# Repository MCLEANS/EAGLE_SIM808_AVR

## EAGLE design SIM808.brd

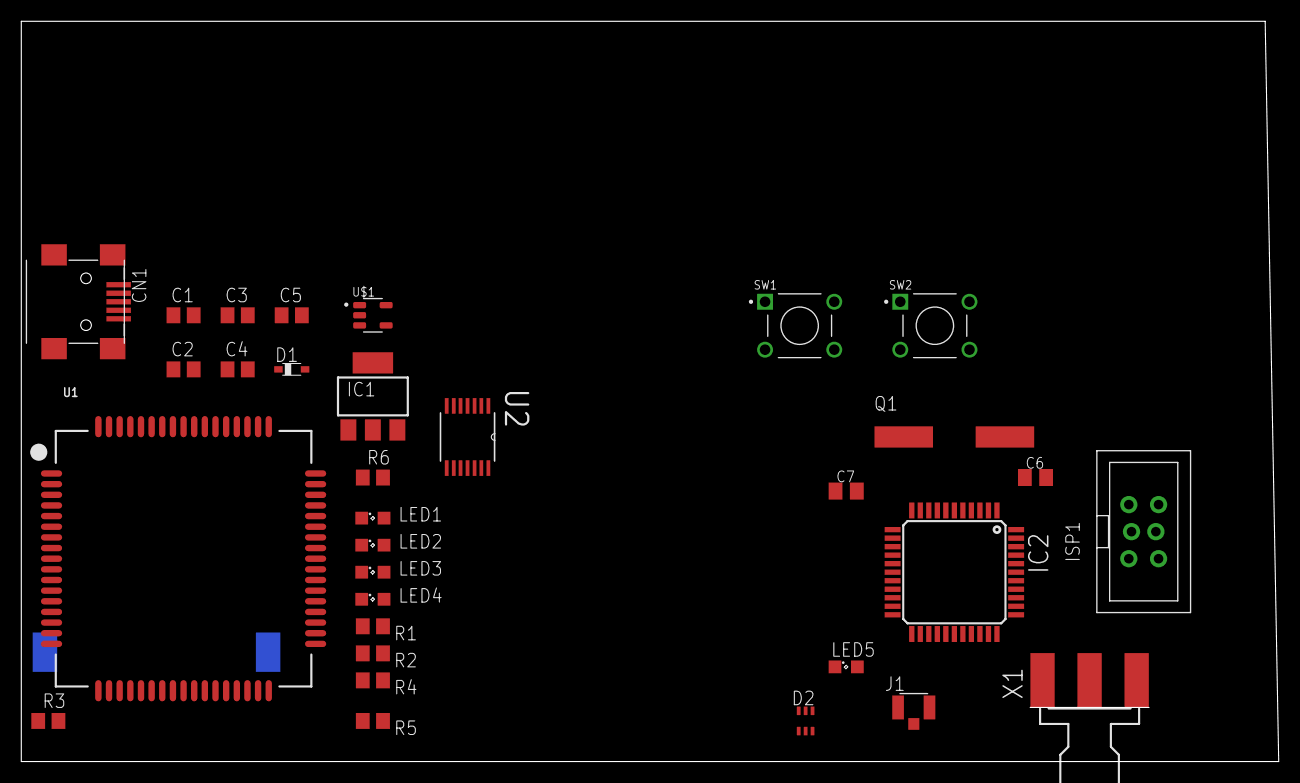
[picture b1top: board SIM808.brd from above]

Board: 2 copper layers, 118.1 x 69.5 mm, 33 parts (1 on the bottom side), 37 nets, no tracks yet.

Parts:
C1, C2: 10uF; C0805
C3: 100uF; C0805
C4: 33pF; C0805
C5: 100PF; C0805
C6, C7: 22pF; C0805K
CN1: USB-MINIB
D1: BAT60J; SOD323_ST
D2: SMF05C; SC70-6
IC1: LM1117S; SOT223
IC2: MEGA32-A; TQFP44
ISP1: AVRISP-BOX
J1: U.FL-R-SMT(01); HRS_U.FL-R-SMT(01)
LED1, LED2, LED3, LED4, LED5: SML0805
Q1: CSM-7X-DU
R1: 470ohm; R0805
R2: 1K; R0805
R3: 10K; R0805
R4, R5, R6: 220ohm; R0805
SW1, SW2: 1825910-2; TE_1825910-2
U1: SIM900_SMT
U2: SN74ABT125PW; SOP65P640X120-14N
U$1: MCP73811T-420I/OT; SOT95P280X145-5N
X1: SMA-142-0701-801/806; J502-ND-142-0701-801/806
X2: 5036_006_201_862

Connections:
1.8V: D2.1, U1.P$29, X2.C1
2.8V: R3.1, U1.P$7
3V3: IC1.2, IC1.4
+5V: C1.1, CN1.VBUS, IC1.3, IC2.5, IC2.17, IC2.27, IC2.29, IC2.38, ISP1.2, LED1.A, U1.P$25, U2.14, U$1.4
GND: C1.2, C2.2, C3.2, C4.2, C5.2, C6.2, C7.2, CN1.GND, CN1.ID, D1.A, D2.2, IC1.1, IC2.6, IC2.18, IC2.28, IC2.39, ISP1.6, J1.1, J1.2, R2.1, R4.2, R5.2, R6.2, SW1.3, SW1.4, SW2.3, SW2.4, U1.P$1, U1.P$2, U1.P$3, U1.P$18, U1.P$28, U1.P$34, U1.P$36, U1.P$40, U1.P$51, U1.P$52, U1.P$54, U1.P$64, U1.P$65, U1.P$67, U1.P$68, U2.1, U2.4, U2.7, U2.10, U2.13, U$1.1, U$1.2, X1.G@1, X1.G@2, X1.G@3, X1.G@4, X2.C5
GSM_RST: SW1.1, SW1.2, U1.P$16
GSM_RXD: IC2.10, U1.P$15
GSM_TXD: U1.P$14, U2.2
GSM_TXD_5V: IC2.9, U2.3
MISO: IC2.2, ISP1.1
MOSI: IC2.1, ISP1.4
unnamed: LED2.A, R1.2, U$1.5
unnamed: LED2.C, R2.2
unnamed: LED1.C, R1.1
unnamed: C2.1, U1.P$17
unnamed: U1.P$66, X1.1
unnamed: J1.3, U1.P$35
unnamed: LED5.C, R6.1
unnamed: R3.2, U1.P$13
unnamed: LED4.C, R5.1
unnamed: LED3.C, R4.1
unnamed: C6.1, IC2.7, Q1.2
unnamed: C7.1, IC2.8, Q1.1
NETSTAT: U1.P$50, U2.5
NETSTAT_5V: LED3.A, U2.6
PWRSTAT: U1.P$49, U2.9
PWRSTAT_5V: LED4.A, U2.8
RESET: IC2.4, ISP1.5, SW2.1, SW2.2
RING: U1.P$10, U2.12
RING_5V: LED5.A, U2.11
SCK: IC2.3, ISP1.3
SIM_CLK: D2.4, U1.P$31, X2.C3
SIM_DATA: D2.3, U1.P$30, X2.C7
SIM_RST: D2.5, U1.P$32, X2.C2
USB_D+: CN1.D+, U1.P$26
USB_D-: CN1.D-, U1.P$27
VBAT: C3.1, C4.1, C5.1, D1.C, U1.P$4, U1.P$5, U1.P$6, U$1.3

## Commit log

2020-03-25 project bare minimum
2020-03-25 SIM808 circuitry design
2020-03-25 routed design
